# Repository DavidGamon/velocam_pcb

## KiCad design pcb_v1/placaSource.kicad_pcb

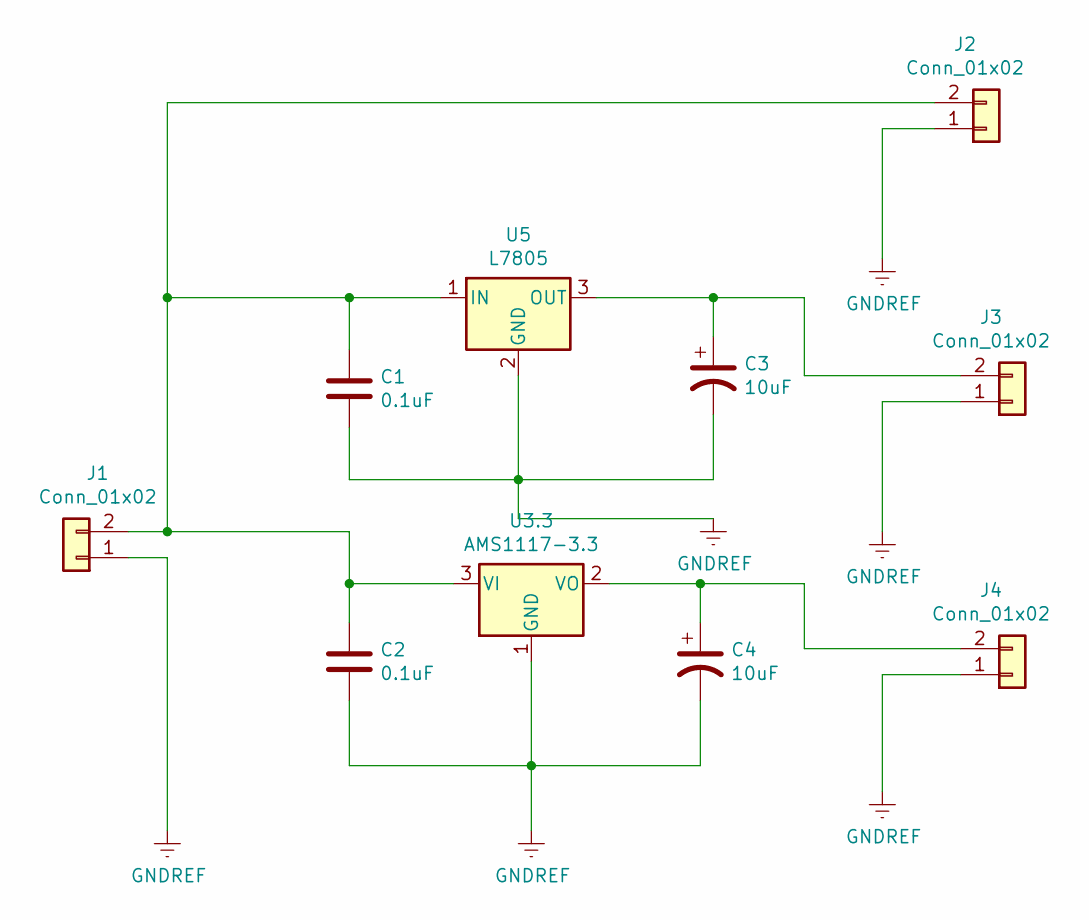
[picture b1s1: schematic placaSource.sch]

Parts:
C1, C2: 0.1uF; C_Axial_L3.8mm_D2.6mm_P7.50mm_Horizontal
C3, C4: 10uF; CP_Radial_Tantal_D7.0mm_P5.00mm
J1: Conn_01x02; TerminalBlock_bornier-2_P5.08mm
J2, J3, J4: Conn_01x02; PinHeader_1x02_P2.54mm_Vertical
U3.3: AMS1117-3.3; SOT-223-3_TabPin2
U5: L7805; TO-220-3_Vertical

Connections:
GNDREF: C1.2, C2.2, C3.2, C4.2, J1.1, J2.1, J3.1, J4.1, U3.3.1 (GND), U5.2 (GND)
unnamed: C1.1, C2.1, J1.2, J2.2, U3.3.3 (VI), U5.1 (IN)
unnamed: C3.1, J3.2, U5.3 (OUT)
unnamed: C4.1, J4.2, U3.3.2 (VO)

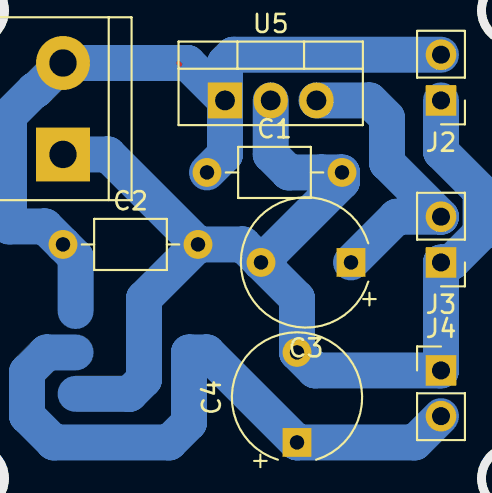
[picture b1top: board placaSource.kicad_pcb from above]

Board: 2 copper layers, 10 parts (1 on the bottom side), 4 nets.

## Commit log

2019-06-04 inicio
2019-06-04 version2
2019-06-04 agregue el commit.txt
2019-06-04 modificacion de commit.txt
2019-06-04 agregue un nuevo commit a commit.txt
2019-06-04 modificacion con nano
2019-06-05 cambio1 develop
2019-06-05 cambio2 develop
2019-06-05 ultima modificacion version 2
2019-06-05 modificacion version 2 y ordenamiento
